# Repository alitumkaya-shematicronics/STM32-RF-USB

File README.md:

# STM32+RF+USB with-KiCad
* STM32 + RF + USB System
This project integrates an STM32 microcontroller with RF communication and USB connectivity. 
The STM32 handles control and data processing, while the RF module enables wireless communication. 
The USB interface allows for data transfer and connection with computers. This setup is ideal for IoT and remote control applications.

# Shematic

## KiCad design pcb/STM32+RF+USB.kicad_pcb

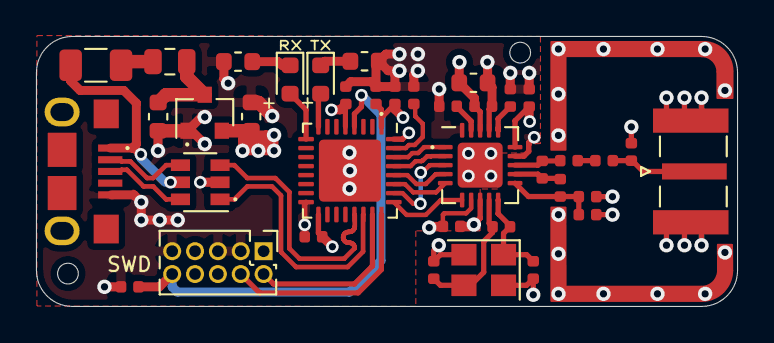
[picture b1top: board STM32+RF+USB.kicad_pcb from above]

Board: 2 copper layers, 39.0 x 15.0 mm, 38 parts (0 on the bottom side), 21 nets.

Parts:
C1, C2, C8: 10u; C_0603_1608Metric
C3, C5, C6, C7: 100n; C_0402_1005Metric
C4: 1u; C_0402_1005Metric
C9, C10, C11: 10n; C_0402_1005Metric
C12: 33n; C_0402_1005Metric
C13, C14: 12p; C_0402_1005Metric
C15: 1p5; C_0402_1005Metric
C16: 1p; C_0402_1005Metric
C17: 2n2; C_0402_1005Metric
C18: 4p7; C_0402_1005Metric
D1: GR; LED_0603_1608Metric
D2: YE; LED_0603_1608Metric
F1: 100mA; Fuse_1206_3216Metric
FB1: 100 @ 100MHz; L_0805_2012Metric
J1: USB_B_Micro; 101181930001LF
J2: SMA; SMA_Samtec_SMA-J-P-X-ST-EM1_EdgeMount
J3: ARM 10pin; PinHeader_2x05_P1.27mm_Vertical
L1: 3n9; L_0402_1005Metric
L2: 8n2; L_0402_1005Metric
L3: 2n7; L_0402_1005Metric
R1: 2k2; R_0402_1005Metric
R2, R3: 2k2; R_0603_1608Metric
R4: 22k; R_0402_1005Metric
R5: 1M; R_0402_1005Metric
U1: XC6206P332MR; SOT-23
U2: USBLC6-2SC6; SOT-23-6
U3: STM32L432KBU6; QFN-32-1EP_5x5mm_P0.5mm_EP3.45x3.45mm
U4: nRF24L01P; QFN-20-1EP_4x4mm_P0.5mm_EP2.5x2.5mm
Y1: 16MHz; Crystal_SMD_3225-4Pin_3.2x2.5mm

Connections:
+3V3: C2.1, C4.1, C5.1, C6.1, C7.1, C8.1, C9.1, C10.1, C11.1, J3.1, U1.2, U3.1, U3.5, U3.17, U4.7, U4.15, U4.18
+5V: F1.2, J1.1, U2.5
GND: C1.2, C2.2, C3.2, C4.2, C5.2, C6.2, C7.2, C8.2, C9.2, C10.2, C11.2, C12.2, C13.2, C14.2, C16.1, C17.1, C18.1, J1.5, J2.2, J3.3, J3.5, J3.9, R1.2, R2.2, R3.2, R4.2, U1.1, U2.2, U3.16, U3.32, U3.33, U4.8, U4.14, U4.17, U4.20, U4.21, Y1.2, Y1.4
NRF_ANT1: L2.2, L3.2, U4.12
NRF_ANT2: L1.1, L2.1, U4.13
NRF_CE: U3.30, U4.1
NRF_IRQ: U3.25, U4.6
NRF_VDD_PA: C17.2, C18.2, L3.1, U4.11
NRF_XC1: C13.1, R5.2, U4.10, Y1.1
NRF_XC2: C14.1, R5.1, U4.9, Y1.3
NRST: C3.1, J3.10, U3.4
SPI3_!CS: U3.29, U4.2
SPI3_MISO: U3.27, U4.5
SPI3_MOSI: U3.28, U4.4
SPI3_SCK: U3.26, U4.3
SWCLK: J3.4, U3.24
SWDIO: J3.2, U3.23
USB_CONN_D+: J1.3, U2.6
USB_CONN_D-: J1.2, U2.4
USB_D+: U2.1, U3.22
USB_D-: U2.3, U3.21

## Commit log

2025-01-12 İnitial commit. Added gittignore file.
